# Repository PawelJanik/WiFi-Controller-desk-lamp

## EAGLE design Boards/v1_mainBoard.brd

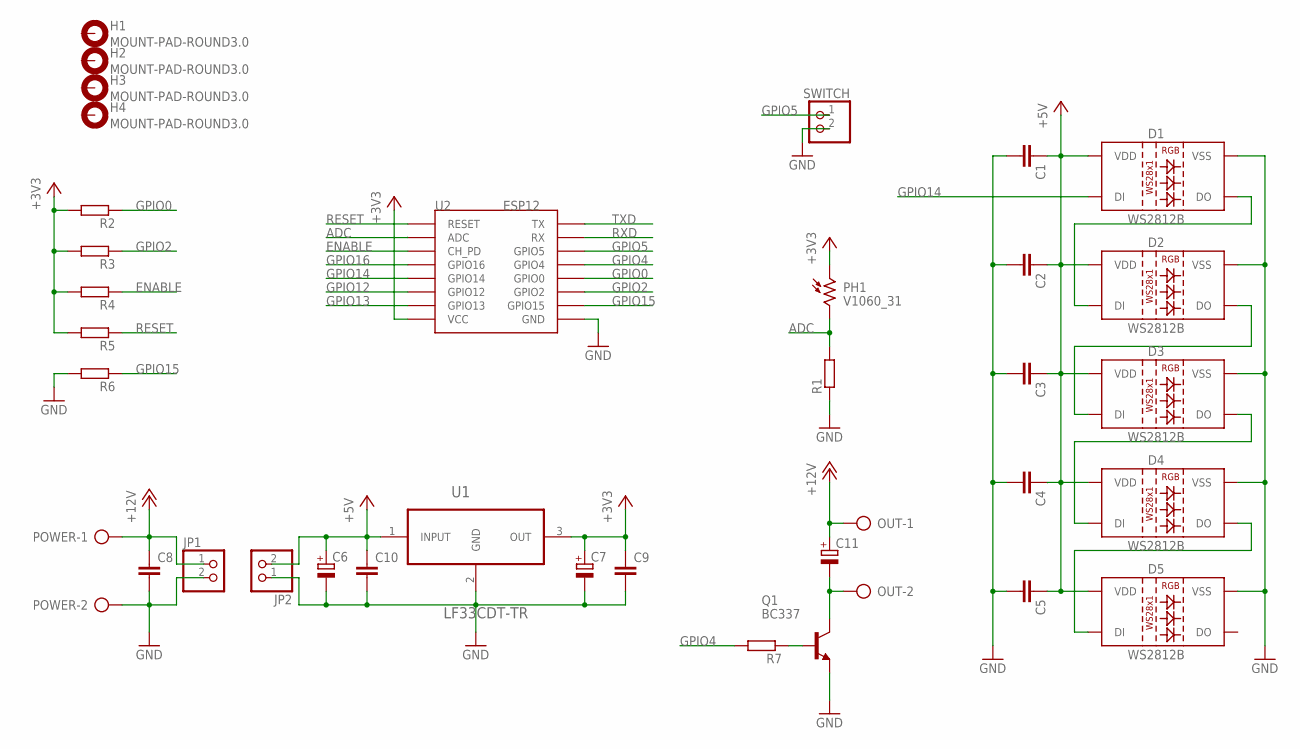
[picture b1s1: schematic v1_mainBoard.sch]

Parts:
C1, C2, C3, C4, C5, C8, C9, C10: C-EUC1206; C1206
C6, C7: CPOL-EUE2.5-6; E2,5-6
C11: CPOL-EUE3.5-8; E3,5-8
D1, D2, D3, D4, D5: WS2812B
H1, H2, H3, H4: MOUNT-PAD-ROUND3.0; 3,0-PAD
JP1, JP2: PINHD-1X2; 1X02
OUT: AK300/2
PH1: V1060_31; TO-5_V10
POWER: AK300/2
Q1: BC337; TO92
R1, R2, R3, R4, R5, R6, R7: R-EU_R1206; R1206
SWITCH: PINHD-1X2; 1X02
U1: LF33CDT-TR; TO228P972X240-3N
U2: ESP12

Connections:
+3V3: C7.+, C9.1, PH1.1, R2.2, R3.2, R4.2, R5.2, U1.3 (OUT), U2.VCC
+5V: C1.1, C2.1, C3.1, C4.1, C5.1, C6.+, C10.1, D1.1 (VDD), D2.1 (VDD), D3.1 (VDD), D4.1 (VDD), D5.1 (VDD), JP2.2, U1.1 (INPUT)
+12V: C8.1, C11.+, JP1.1, OUT.1, POWER.1
ADC: PH1.2, R1.2, U2.ADC
ENABLE: R4.1, U2.CH_PD
GND: C1.2, C2.2, C3.2, C4.2, C5.2, C6.-, C7.-, C8.2, C9.2, C10.2, D1.3 (VSS), D2.3 (VSS), D3.3 (VSS), D4.3 (VSS), D5.3 (VSS), JP1.2, JP2.1, POWER.2, Q1.1 (E), R1.1, R6.2, SWITCH.2, U1.2 (GND), U2.GND
GPIO0: R2.1, U2.GPIO0
GPIO2: R3.1, U2.GPIO2
GPIO4: R7.2, U2.GPIO5 (GPIO4)
GPIO5: SWITCH.1, U2.GPIO4 (GPIO5)
GPIO12: U2.GPIO12
GPIO13: U2.GPIO13
GPIO14: D1.4 (DI), U2.GPIO14
GPIO15: R6.1, U2.GPIO15
GPIO16: U2.GPIO16
unnamed: C11.-, OUT.2, Q1.3 (C)
unnamed: Q1.2 (B), R7.1
unnamed: D1.2 (DO), D2.4 (DI)
unnamed: D2.2 (DO), D3.4 (DI)
unnamed: D3.2 (DO), D4.4 (DI)
unnamed: D4.2 (DO), D5.4 (DI)
RESET: R5.1, U2.RESET
RXD: U2.RX
TXD: U2.TX

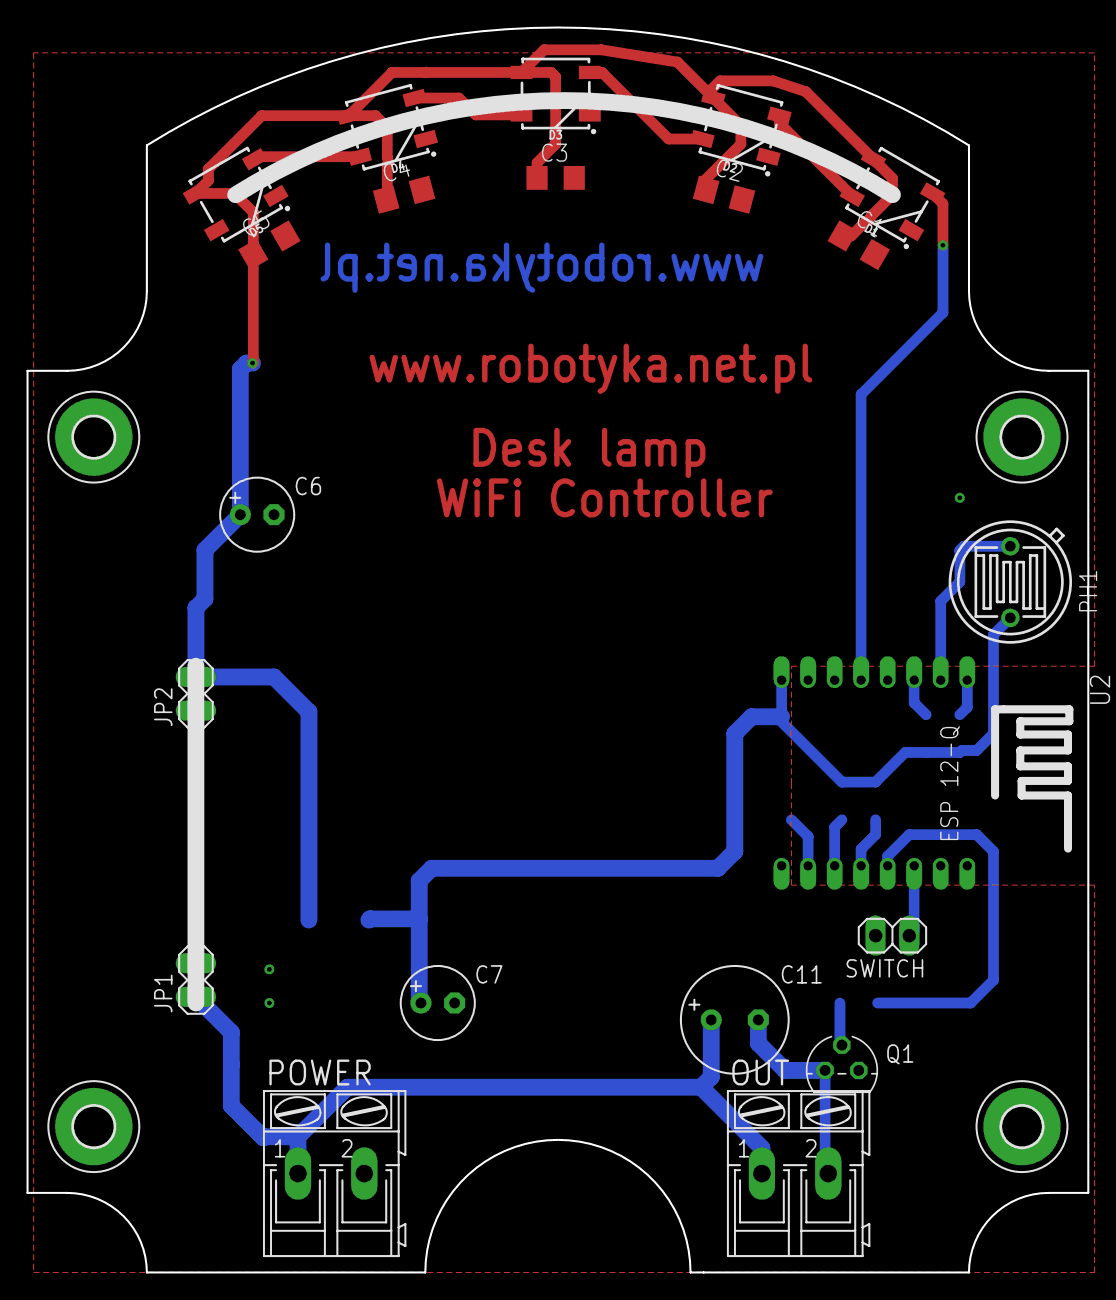
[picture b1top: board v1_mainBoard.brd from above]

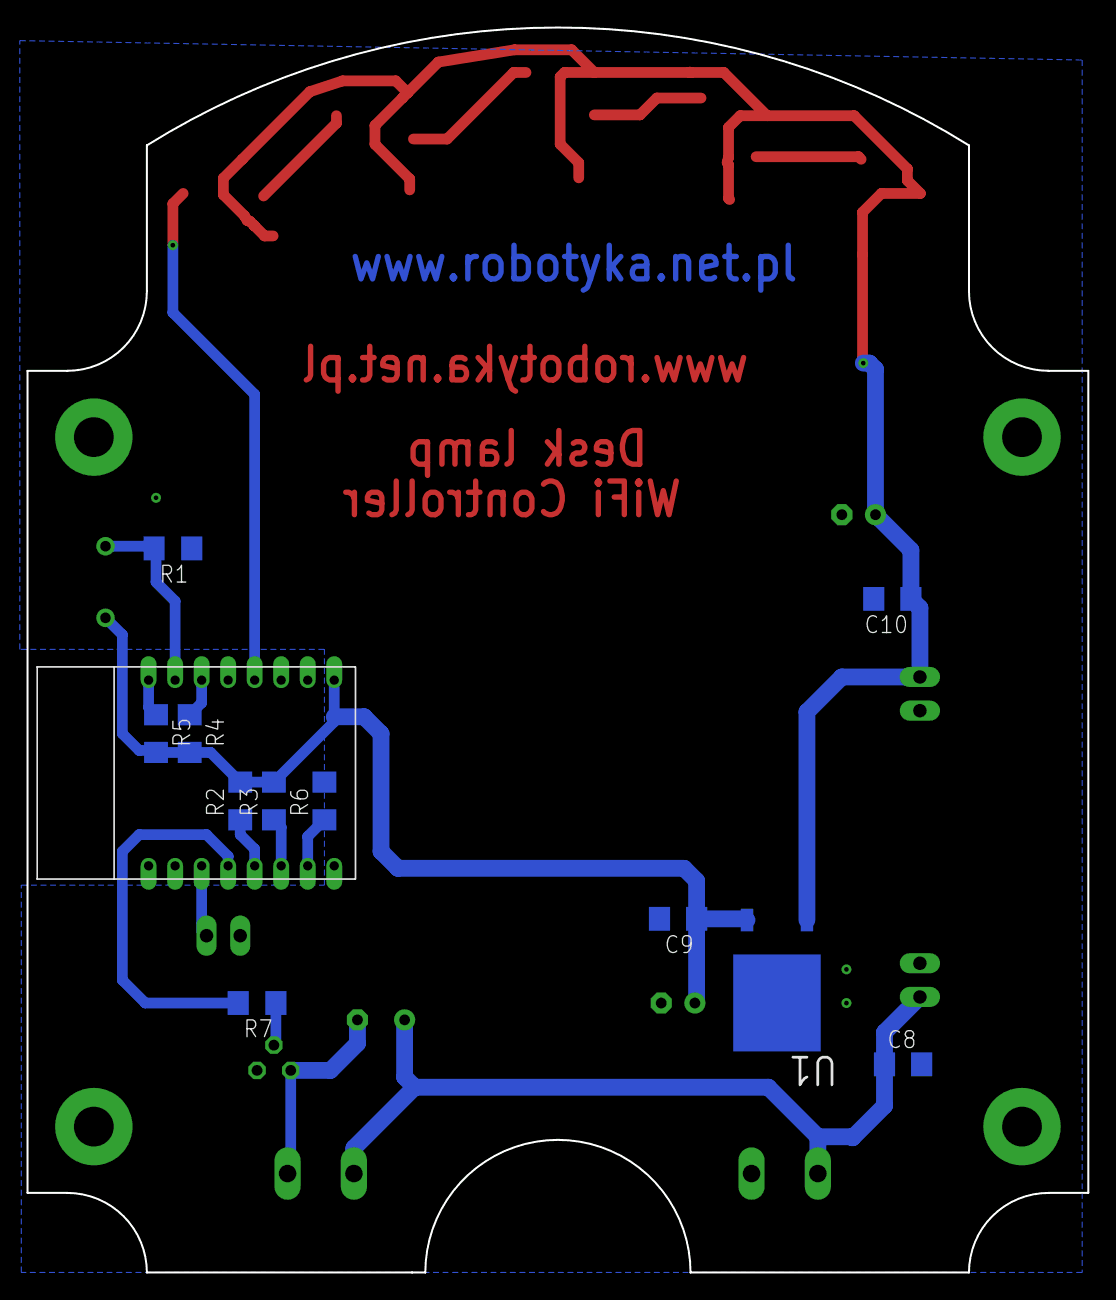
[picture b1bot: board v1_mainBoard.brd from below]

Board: 2 copper layers, 80.0 x 93.9 mm, 36 parts (11 on the bottom side), 19 nets.

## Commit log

2019-02-02 Update
    Fixed switch error and add dxf file for laser cutting steel plate.
2019-02-05 fixed problems with vibration of switch contacts
